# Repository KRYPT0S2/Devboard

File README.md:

# rp2040 devboard

> **pinout heads-up:** even though this uses two 1x20 2.54mm headers (`J1` and `J3`), **it is NOT pin-compatible with raspberry pi pico shields/carriers**. `VBUS` is on pin 1 of `J3` instead of pin 40, so check the pinout table below before plugging it into anything pre-made.

## specs
- **MCU:** raspberry pi rp2040
- **flash:** gigadevice `GD25Q32EEIGR` 
- **clock:** 12 mhz 3225 crystal 
- **regulator:** `XC6206P332MR-G` 
- **usb c:** 14-pin usb 2.0 type-c receptacle 
- **buttons and debug:** tactile `BOOTSEL` button
- **PCB and case:** 2-layer 1.6mm fr4 board assembled via jlcpcb economic pcba

## pinout

### left header (`J1`, top to bottom)
| pin | net | notes | pin | net | notes |
| :---: | :--- | :--- | :---: | :--- | :--- |
| **1** | `GP0` | spi0 rx / i2c0 sda / uart0 tx | **11** | `GP8` | spi1 rx / i2c0 sda / uart1 tx |
| **2** | `GP1` | spi0 csn / i2c0 scl / uart0 rx | **12** | `GP9` | spi1 csn / i2c0 scl / uart1 rx |
| **3** | `GND` | ground | **13** | `GND` | ground |
| **4** | `GP2` | spi0 sck / i2c1 sda | **14** | `GP10` | spi1 sck / i2c1 sda |
| **5** | `GP3` | spi0 tx / i2c1 scl | **15** | `GP11` | spi1 tx / i2c1 scl |
| **6** | `GP4` | spi0 rx / i2c0 sda / uart1 tx | **16** | `GP12` | spi1 rx / i2c0 sda / uart0 tx |
| **7** | `GP5` | spi0 csn / i2c0 scl / uart1 rx | **17** | `GP13` | spi1 csn / i2c0 scl / uart0 rx |
| **8** | `GND` | ground | **18** | `GND` | ground |
| **9** | `GP6` | spi0 sck / i2c1 sda | **19** | `GP14` | spi1 sck / i2c1 sda |
| **10** | `GP7` | spi0 tx / i2c1 scl | **20** | `GP15` | spi1 tx / i2c1 scl |

### right header (`J3`, top to bottom)
| pin | net | notes | pin | net | notes |
| :---: | :--- | :--- | :---: | :--- | :--- |
| **1** | `VBUS` | 5v usb power input | **11** | `RUN` | active-low rp2040 reset |
| **2** | `GP29` | `ADC3` | **12** | `GP22` | digital gpio |
| **3** | `GND` | ground | **13** | `GND` | ground |
| **4** | `GP28` | `ADC2` | **14** | `GP21` | digital gpio |
| **5** | `+3V3` | 3.3v regulated output | **15** | `GP20` | digital gpio |
| **6** | `GP27` | `ADC1` | **16** | `GP19` | spi0 tx / i2c1 scl |
| **7** | `GP26` | `ADC0` | **17** | `GP18` | spi0 sck / i2c1 sda |
| **8** | `GND` | ground | **18** | `GND` | ground |
| **9** | `GP24` | digital gpio | **19** | `GP17` | spi0 csn / i2c0 scl / uart0 rx |
| **10** | `GP23` | digital gpio | **20** | `GP16` | spi0 rx / i2c0 sda / uart0 tx |

### bottom swd header (`J2`, left to right)
- **pin 1:** `SWCLK`
- **pin 2:** `GND`
- **pin 3:** `SWD` (`SWDIO`)

# Bill of Materials (BOM)

| Sr.No | Component | Qty | Source | Unit Price (INR) | Shipping (INR) | Total (INR) | Total (USD) |
| :---: | :--- | :---: | :--- | :---: | :---: | :---: | :---: |
| **1** | **RP2040 Devboard PCB + PCBA** | 1 order | [JLCPCB.com](https://jlcpcb.com/) | ₹3,098.30 | ₹884.17 | ₹3,982.47 | $42.97 |
| **2** | **2.54mm 1x40 Pin Male Single Row Straight Short Header Strip** | 12 strips | [Robu.in](https://robu.in/product/2-54mm-1x40-pin-male-single-row-straight-short-header-strip-pack-of-3/) | ₹84.00 | ₹49.00 | ₹133.00 | $1.44 |
| **—** | **Grand Total** | — | — | **₹3,182.30** | **₹933.17** | **₹4,115.47** | **$44.41** |

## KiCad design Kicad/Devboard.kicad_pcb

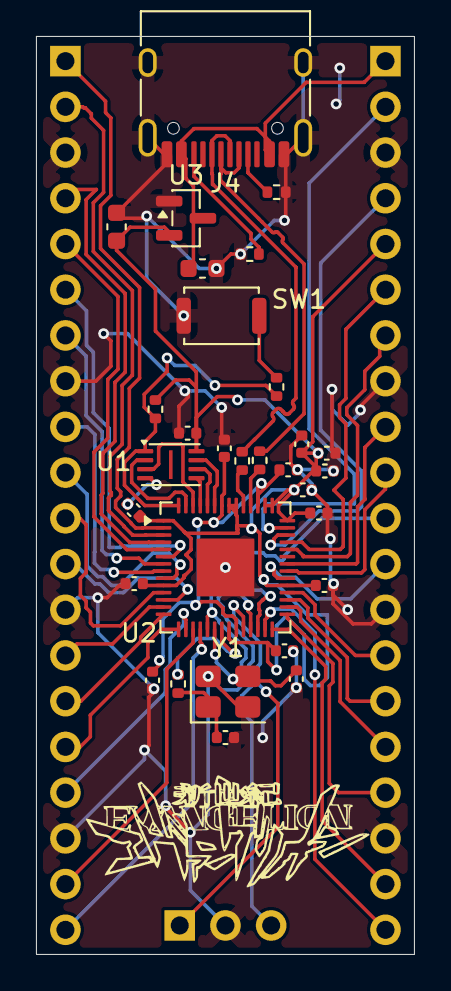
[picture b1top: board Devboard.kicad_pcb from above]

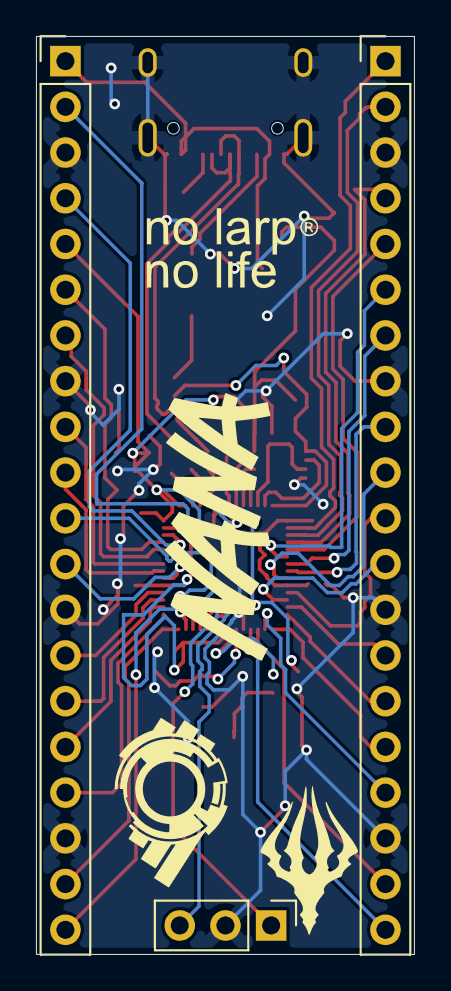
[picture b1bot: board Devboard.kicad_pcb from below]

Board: 2 copper layers, 21.0 x 51.0 mm, 33 parts (3 on the bottom side), 52 nets.

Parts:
C1, C2, C5, C6, C7, C8, C9, C10, C11, C13, C14: 0.1uF; C_0402_1005Metric
C3, C4: 33pF; C_0402_1005Metric
C12, C15: 1uF; C_0402_1005Metric
C16, C17: 10uF; C_0603_1608Metric
J2, J3: Conn_01x20; PinHeader_1x20_P2.54mm_Vertical
J4: USB_C_Receptacle_USB2.0_14P; USB_C_Receptacle_HRO_TYPE-C-31-M-12
J4#2: Conn_01x03; PinHeader_1x03_P2.54mm_Vertical
R1, R3: 1k; R_0402_1005Metric
R2: 10k; R_0402_1005Metric
R4, R5: 27; R_0402_1005Metric
R6, R7: 5.1k; R_0402_1005Metric
SW1: SW_Push; SW_Push_SPST_NO_Alps_SKRK
U1: W25Q128JVS; Winbond_USON-8-1EP_3x2mm_P0.5mm_EP0.2x1.6mm
U2: RP2040; QFN-56-1EP_7x7mm_P0.4mm_EP3.2x3.2mm
U3: MCP1700x-330xxTT; SOT-23
Y1: 12MHz; Crystal_SMD_3225-4Pin_3.2x2.5mm

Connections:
+1V1: C13.1, C14.1, C15.1, U2.23 (DVDD), U2.45 (VREG_VOUT), U2.50 (DVDD)
+3V3: C1.1, C2.1, C5.1, C6.1, C7.1, C8.1, C9.1, C10.1, C11.1, C12.1, C17.1, J3.5, R2.2, U1.8 (VCC), U2.1 (IOVDD), U2.10 (IOVDD), U2.22 (IOVDD), U2.33 (IOVDD), U2.42 (IOVDD), U2.43 (ADC_AVDD), U2.44 (VREG_VIN), U2.48 (USB_VDD), U2.49 (IOVDD), U3.2 (VO)
GND: C1.2, C2.2, C3.1, C4.1, C5.2, C6.2, C7.2, C8.2, C9.2, C10.2, C11.2, C12.2, C13.2, C14.2, C15.2, C16.2, C17.2, J2.3, J2.8, J2.13, J2.18, J3.3, J3.8, J3.13, J3.18, J4.A1 (GND), J4.A12 (GND), J4.B1 (GND), J4.B12 (GND), J4.SH (SHIELD), J4#2.2, R6.2, R7.2, SW1.1, U1.4 (GND), U2.19 (TESTEN), U2.57 (GND), U3.1 (GND), Y1.2 (G), Y1.4 (G)
GP0: J2.1, U2.2 (GPIO0)
GP1: J2.2, U2.3 (GPIO1)
GP2: J2.4, U2.4 (GPIO2)
GP3: J2.5, U2.5 (GPIO3)
GP4: J2.6, U2.6 (GPIO4)
GP5: J2.7, U2.7 (GPIO5)
GP6: J2.9, U2.8 (GPIO6)
GP7: J2.10, U2.9 (GPIO7)
GP8: J2.11, U2.11 (GPIO8)
GP9: J2.12, U2.12 (GPIO9)
GP10: J2.14, U2.13 (GPIO10)
GP11: J2.15, U2.14 (GPIO11)
GP12: J2.16, U2.15 (GPIO12)
GP13: J2.17, U2.16 (GPIO13)
GP14: J2.19, U2.17 (GPIO14)
GP15: J2.20, U2.18 (GPIO15)
GP16: J3.20, U2.27 (GPIO16)
GP17: J3.19, U2.28 (GPIO17)
GP18: J3.17, U2.29 (GPIO18)
GP19: J3.16, U2.30 (GPIO19)
GP20: J3.15, U2.31 (GPIO20)
GP21: J3.14, U2.32 (GPIO21)
GP22: J3.12, U2.34 (GPIO22)
GP23: J3.10, U2.35 (GPIO23)
GP24: J3.9, U2.36 (GPIO24)
GP26 ADC0: J3.7, U2.38 (GPIO26/ADC0)
GP27 ADC1: J3.6, U2.39 (GPIO27/ADC1)
GP28 ADC2: J3.4, U2.40 (GPIO28/ADC2)
GP29 ADC3: J3.2, U2.41 (GPIO29/ADC3)
unnamed: C4.2, R3.1, Y1.1
unnamed: J4.A5 (CC1), R6.1
unnamed: J4.B5 (CC2), R7.1
unnamed: R1.2, SW1.2
unnamed: R4.1, U2.46 (USB_DM)
unnamed: R5.1, U2.47 (USB_DP)
RUN: J3.11, U2.26 (RUN)
SCLK: U1.6 (CLK), U2.52 (QSPI_SCLK)
SD0: U1.5 (DI/IO_{0}), U2.53 (QSPI_SD0)
SD1: U1.2 (DO/IO_{1}), U2.55 (QSPI_SD1)
SD2: U1.3 (~WP/IO_{2}), U2.54 (QSPI_SD2)
SD3: U1.7 (~HOLD/~RESET/IO_{3}), U2.51 (QSPI_SD3)
SS: R1.1, R2.1, U1.1 (~CS), U2.56 (~QSPI_SS)
SWCLK: J4#2.1, U2.24 (SWCLK)
SWD: J4#2.3, U2.25 (SWDIO)
VBUS: C16.1, J3.1, J4.A4 (VBUS), J4.A9 (VBUS), J4.B4 (VBUS), J4.B9 (VBUS), U3.3 (VI)
Xin: C3.2, U2.20 (XIN), Y1.3
Xout: R3.2, U2.21 (XOUT)
d+: J4.A6 (D+), J4.B6 (D+), R5.2
d-: J4.A7 (D-), J4.B7 (D-), R4.2
